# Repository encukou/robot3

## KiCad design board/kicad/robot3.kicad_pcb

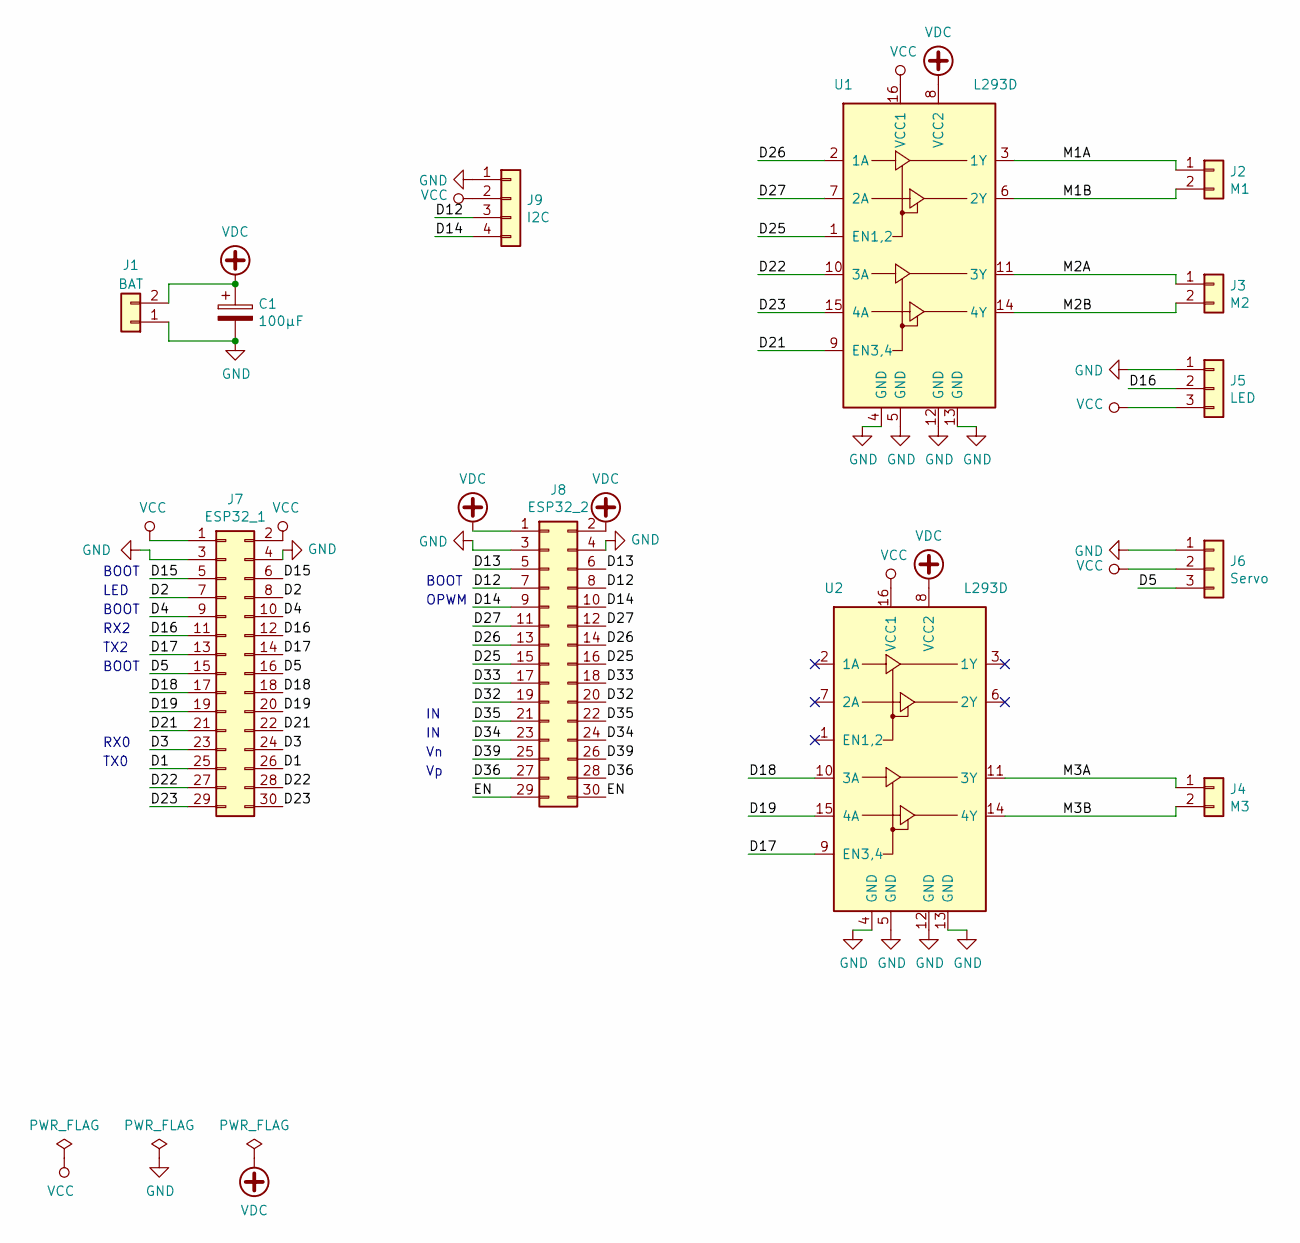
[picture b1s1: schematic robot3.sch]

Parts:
C1: 100μF; CP_Radial_D5.0mm_P2.50mm
J1: BAT; JST_XH_B2B-XH-A_1x02_P2.50mm_Vertical
J2: M1; JST_XH_B2B-XH-A_1x02_P2.50mm_Vertical
J3: M2; JST_XH_B2B-XH-A_1x02_P2.50mm_Vertical
J4: M3; JST_XH_B2B-XH-A_1x02_P2.50mm_Vertical
J5: LED; PinHeader_1x03_P2.54mm_Vertical
J6: Servo; PinHeader_1x03_P2.54mm_Vertical
J7: ESP32_1; PinSocket_2x15_P2.54mm_Vertical
J8: ESP32_2; PinSocket_2x15_P2.54mm_Vertical
J9: I2C; PinSocket_1x04_P2.54mm_Vertical
U1, U2: L293D; DIP-16_W7.62mm

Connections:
/D1: J7.25, J7.26
/D2: J7.7, J7.8
/D3: J7.23, J7.24
/D4: J7.9, J7.10
/D5: J6.3, J7.15, J7.16
/D12: J8.7, J8.8, J9.3
/D13: J8.5, J8.6
/D14: J8.9, J8.10, J9.4
/D15: J7.5, J7.6
/D16: J5.2, J7.11, J7.12
/D17: J7.13, J7.14, U2.9 (EN3,4)
/D18: J7.17, J7.18, U2.10 (3A)
/D19: J7.19, J7.20, U2.15 (4A)
/D21: J7.21, J7.22, U1.9 (EN3,4)
/D22: J7.27, J7.28, U1.10 (3A)
/D23: J7.29, J7.30, U1.15 (4A)
/D25: J8.15, J8.16, U1.1 (EN1,2)
/D26: J8.13, J8.14, U1.2 (1A)
/D27: J8.11, J8.12, U1.7 (2A)
/D32: J8.19, J8.20
/D33: J8.17, J8.18
/D34: J8.23, J8.24
/D35: J8.21, J8.22
/D36: J8.27, J8.28
/D39: J8.25, J8.26
/EN: J8.29, J8.30
/M1A: J2.1, U1.3 (1Y)
/M1B: J2.2, U1.6 (2Y)
/M2A: J3.1, U1.11 (3Y)
/M2B: J3.2, U1.14 (4Y)
/M3A: J4.1, U2.11 (3Y)
/M3B: J4.2, U2.14 (4Y)
GND: C1.2, J1.1, J5.1, J6.1, J7.3, J7.4, J8.3, J8.4, J9.1, U1.4 (GND), U1.5 (GND), U1.12 (GND), U1.13 (GND), U2.4 (GND), U2.5 (GND), U2.12 (GND), U2.13 (GND)
VCC: J5.3, J6.2, J7.1, J7.2, J9.2, U1.16 (VCC1), U2.16 (VCC1)
VDC: C1.1, J1.2, J8.1, J8.2, U1.8 (VCC2), U2.8 (VCC2)

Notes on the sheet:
TX0
RX0
LED
BOOT
OPWM
RX2
TX2

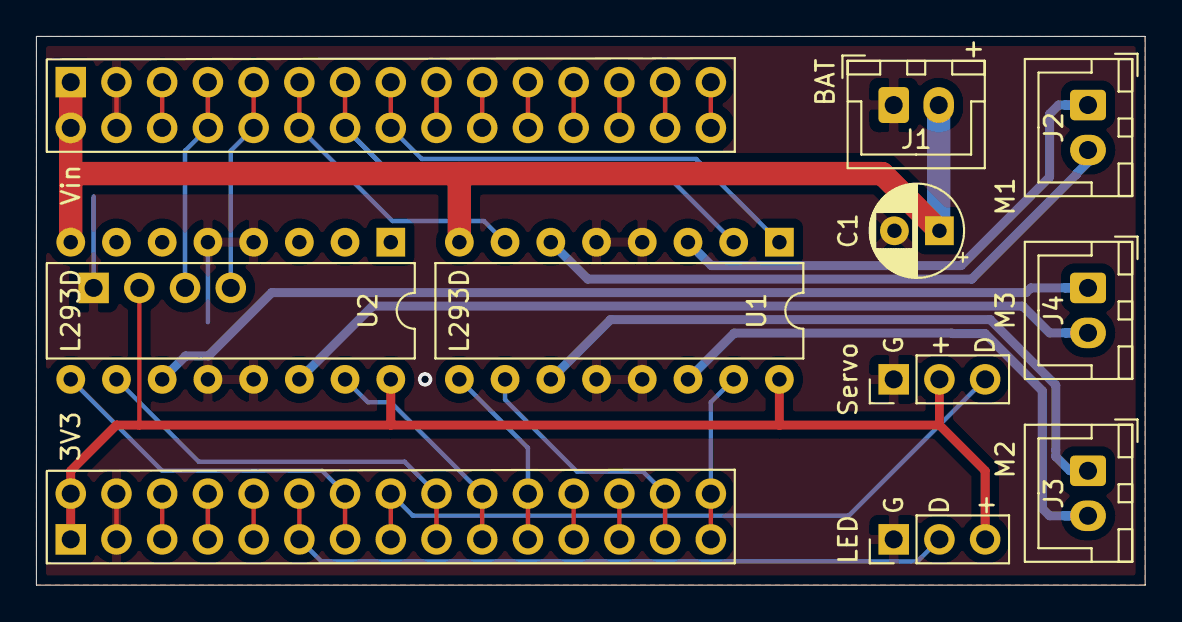
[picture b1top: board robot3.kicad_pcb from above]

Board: 2 copper layers, 61.6 x 30.5 mm, 12 parts (1 on the bottom side), 35 nets.

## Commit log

2019-04-20 Add motors and wi-fi receiving code
2019-04-20 Control motors over uasyncio
2019-04-20 Brake when speed is set to 0
2019-04-20 Don't disconnect after blank line
2019-04-20 Ignore read errors
2019-04-20 Add a joystick app
2019-04-20 Mouse-wheel scroll to rotate
2019-04-20 Add keyboard-based movement & rotation
2019-04-21 Play around with OpenCV
2019-04-21 Calculate motor velocities from marker positions (hacky!)
2019-04-21 Some clean-up
2019-04-22 Detect markers before drawing over them
2019-04-22 Add network commands to cv_control drive
2019-09-28 Add a robot motor holder
2019-09-28 Add an omniwheel adapter
2019-09-28 Some motor holder improvements
2019-11-08 Second prototype
2019-11-15 robot3: Third demo printing
2019-12-18 Adjust the wheel adapter cap
2019-12-18 Add first version of the PCB/battery holder
2019-12-18 Add AP mode and adjust pin/motors numbers/directions
2019-12-28 Add KiCad files
2020-01-13 Move models to subfolder
